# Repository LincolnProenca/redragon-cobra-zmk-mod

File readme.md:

# Custom ZMK Wireless Mouse: Redragon Cobra Mod 🖱️🐍

> **Hardware & Firmware Engineering Portfolio**

A comprehensive hardware and firmware project focused on creating a custom wireless mouse, built upon the Zephyr/ZMK ecosystem. A core idea behind this project was to create a versatile tool that seamlessly transitions between my work and home environments.

The project involved **designing a custom PCB**, specifically tailored to fit perfectly within the ergonomic shell of a **Redragon Cobra**. A key goal was to reuse as many components from the original mouse as possible—such as the switches and the wheel mechanism—transforming a traditional wired mouse into a premium, high-performance wireless tool.

Focused on energy efficiency, multiple productivity layers (Office/Gaming), and RGB Underglow lighting, the development overcame several electrical and logical challenges, especially in integrating high-consumption components (LEDs) with a _low-power_ sensor architecture.

## 📸 Project Gallery (Build Log)

<div align="center">

</div>
<br/>
<div align="center">

</div>

## 🛠️ Hardware Specifications & Custom PCB

The hardware architecture was custom-developed to reuse the Redragon Cobra shell and its main functional components (like the original clicks and side switches). The integration includes:

- **Microcontroller:** SuperMini nRF52 (nice!nano alternative based on the nRF52840)
- **Optical Sensor:** PixArt PMW3610 (Since the original was a wired sensor, it was replaced with this Low-Power architecture ideal for wireless)
- **Scroll / Wheel:** TTC Gold 13mm Rotary Encoder (The original encoder was damaged and an exact replacement wasn't available, so it was swapped for this equivalent TTC Gold)
- **Lighting:** WS2812 LED Strip (9 LEDs for underglow)
- **Battery:** 1200mAh 3.7V LiPo (Model 503048, 5x30x48mm)
- **LED Power Control:** Two-stage power-gating circuit (level shifter): an **A19T P-channel MOSFET**(salvaged from a damaged SuperMini) switches the raw battery line (B+) to the LED strip VCC, and its gate is driven by an **SS8050 NPN transistor** (label Y1, salvaged from the original Redragon Cobra PCB) acting as a level shifter. The NPN base is driven by the MCU's `EXT_POWER` pin (GPIO 1.11) through a ~1.4k base resistor (also salvaged from the damaged SuperMini). This guarantees full enhancement and full cut-off of the MOSFET across the entire battery range (3.0V–4.2V).

## ✨ Features and Functionalities

The firmware was designed to act as a hybrid device (Mouse + Keyboard), allowing the execution of complex macros and direct shortcuts on the board.

### Layer System

- **Gaming Layer (Default):** Standard mouse commands (LCLK, RCLK, MCLK, MB4, MB5) with high-sensitivity scroll.
- **Office Layer:** Transforms the mouse into a productivity tool focused on **Simulink** environments. Features built-in macros (`Ctrl + .`, `C`, `E`, `N`, `T`, `E`, `R`) injected in 30ms for quick alignments, compiling, and block organization.
- **Utility Layer (Bluetooth Modifier):** Holding the "Top 3" button transforms the main clicks into a Bluetooth remote control (Force Slot 0, Force Slot 1, Format Memory).

### Physical Combos

- **TOP_1 + TOP_2:** Clean Soft Off (cuts `EXT_POWER` first, then enters deep sleep).
- **TOP_1 + TOP_3:** Toggle RGB On/Off.
- **TOP_2 + TOP_3:** Next RGB effect.
- **SIDE_1 + SIDE_2:** System Reset (Hardware sys_reset).
- **Bottom Button:** Directly triggers System Reset.

> Combos were deliberately moved off the main click buttons (LMB/RMB/MMB): any key position participating in a combo is held for up to `timeout-ms` on every press, which added perceptible latency to middle-click drags.

## ⚡ Engineering Notes & Hardware Solutions

During development, several electrical integration and mechanical design bottlenecks were resolved. If you intend to replicate this project, pay attention to the following design decisions and topology rules:

### 1. PCB Modeling and Component Alignment

Without schematics for the original Redragon Cobra PCB, the new board had to be modeled from scratch. The PCB outline and component placements were reverse-engineered using top-down photos of the original board and a physical ruler for scale.

### 2. 3D Modeling for Fitment Check

To ensure the SuperMini, LiPo battery, and all reused components would fit within the limited internal space of the original shell, a full 3D model of the assembly was created. This step was crucial to guarantee clearance for the new components without modifying the external plastics.

### 3. Wired to Wireless Conversion Challenges

Because the original Redragon Cobra was a wired mouse, several structural challenges were addressed:

- **Sensor Swap:** The original power-hungry wired sensor had to be replaced by the low-power PixArt PMW3610.
- **Charging Port Routing:** To utilize the original cable exit hole at the front of the mouse for charging, a custom-made male-to-female USB-C cable was fabricated. It routes power from the front of the mouse internally back to the SuperMini microcontroller.

### 4. Power Separation (Brownout Prevention)

The 9-LED WS2812 strip consumes up to ~180mA, which exceeds the chronic regulation capacity of the board's LDO, causing a _brownout_ (VCC drop to ~2.6V) if powered by the 3.3V pin.

- **Solution:** The board's VCC NPN Level Shifter + P-MOSFET)
  By default, WS2812 LEDs continuously drain quiescent current even when turned off (displaying black color) via software. To properly maximize battery life during sleep states, a hardware switch was implemented.

**The design constraint:** the LED strip is powered directly from the raw battery rail (B+), which swings between ~3.0V and 4.2V, while the MCU GPIOs only swing between 0V and 3.3V. Driving the gate of a P-channel MOSFET directly from a 3.3V GPIO is therefore unreliable: with a full battery (4.1V–4.2V), a logic-high GPIO produces a VGS of only about **-0.8V**, which is dangerously close to the low threshold voltage (VGS_th) of the A19T. A proper high-side switch needs the gate to be pulled all the way up to the source voltage (B+) to guarantee cut-off, and all the way down to GND to guarantee full enhancement — something a 3.3V GPIO cannot do on its own.

- **Solution (Hardware — two-stage level shifter):** The gate drive is handled by an **SS8050 NPN transistor** (label Y1, salvaged from the original Redragon Cobra PCB) wired as an open-collector level shifter:
  - **A19T P-MOSFET:** Source -> B+, Drain -> LED VCC, with a **10k pull-up resistor between Gate and Source** (keeps the MOSFET fully off by default).
  - **SS8050 NPN:** Collector -> A19T Gate, Emitter -> GND, Base -> `EXT_POWER` GPIO **1.11** through a **~1.4k base resistor** (salvaged from a damaged SuperMini).
- **How it works:** when `EXT_POWER` is low, the NPN is cut off and the 10k resistor pulls the gate up to B+ (VGS = 0V), fully turning the MOSFET off regardless of battery voltage. When `EXT_POWER` goes high (3.3V), the NPN saturates and pulls the gate to GND, producing VGS = -B+ (up to -4.2V), fully enhancing the MOSFET with minimal RDS(on). Both states are now referenced to the correct rails, so the circuit switches cleanly across the whole battery range with no leakage and no heating.

### 6. Boot Noise (LEDs flashing electronic junk)

When powering up the board, the nRF52 has floating pins that injected noise into the WS2812 strip's data channel.

- **Solution (`.overlay`):** Insertion of the `bias-pull-down;` property on the `pinctrl` MOSI pin to anchor the signal at 0V during boot, coupled with the initialization delay `init-delay-ms = <350>;` to wait for the strip's capacitors.

### 7. Physical Surface Conditioning

**Known Limitation:** The PixArt PMW3610 has extremely weak optical emission to save battery. It **does not work properly on wool or felt mousepads**, as the three-dimensional fibers blur the lens. It requires the use of traditional microfiber (cloth/fabric) mousepads or rigid surfaces.

### 8. PCB Rev1 Limitations & Rev2 Updates

**Known Limitation (Rev1):** Revision 1 (rev1) of the custom PCB does not natively route the Battery (B+) directly to the LED's VCC, nor does it include footprints for the power-gating circuit. These modifications (A19T P-MOSFET, SS8050 NPN, and resistors) had to be manually bodged (hardwired) onto the physical board.

**Rev2 Architecture Overhaul:** To eliminate the bulky discrete transistor assembly, the **Revision 2 (rev2)** of the PCB replaces the entire BJT+MOSFET circuit with a single **TPS22917DBV Load Switch** (SOT-23-6). 

- **How it works:** The raw battery line (B+) connects directly to `VIN`, and the MCU's `EXT_POWER` pin (GPIO 1.11) drives the `ON` pin directly. Since the TPS22917 features an internal smart level-shifter, it seamlessly interfaces a 3.3V GPIO with the fluctuating 3.0V–4.2V battery rail, ensuring a clean cut-off with sub-microampere leakage current.
- **Quick Discharge:** The `QOD` pin is tied directly to `VOUT` to leverage the internal 150Ω discharge resistor, instantly draining the LED strip's capacitors during sleep transitions.

> [!WARNING]
> **Rev2 Disclaimer:** While the Rev2 layout integrates these native traces, capacitors (1μ F input / 0.1μ F output), and the SOT-23-6 footprint, **this board revision has not been physically manufactured or tested yet**. If you plan to order it, please review the schematics and Gerber files carefully.

---

_Status: v1.0 (Full logical functionality validated in Hardware)._

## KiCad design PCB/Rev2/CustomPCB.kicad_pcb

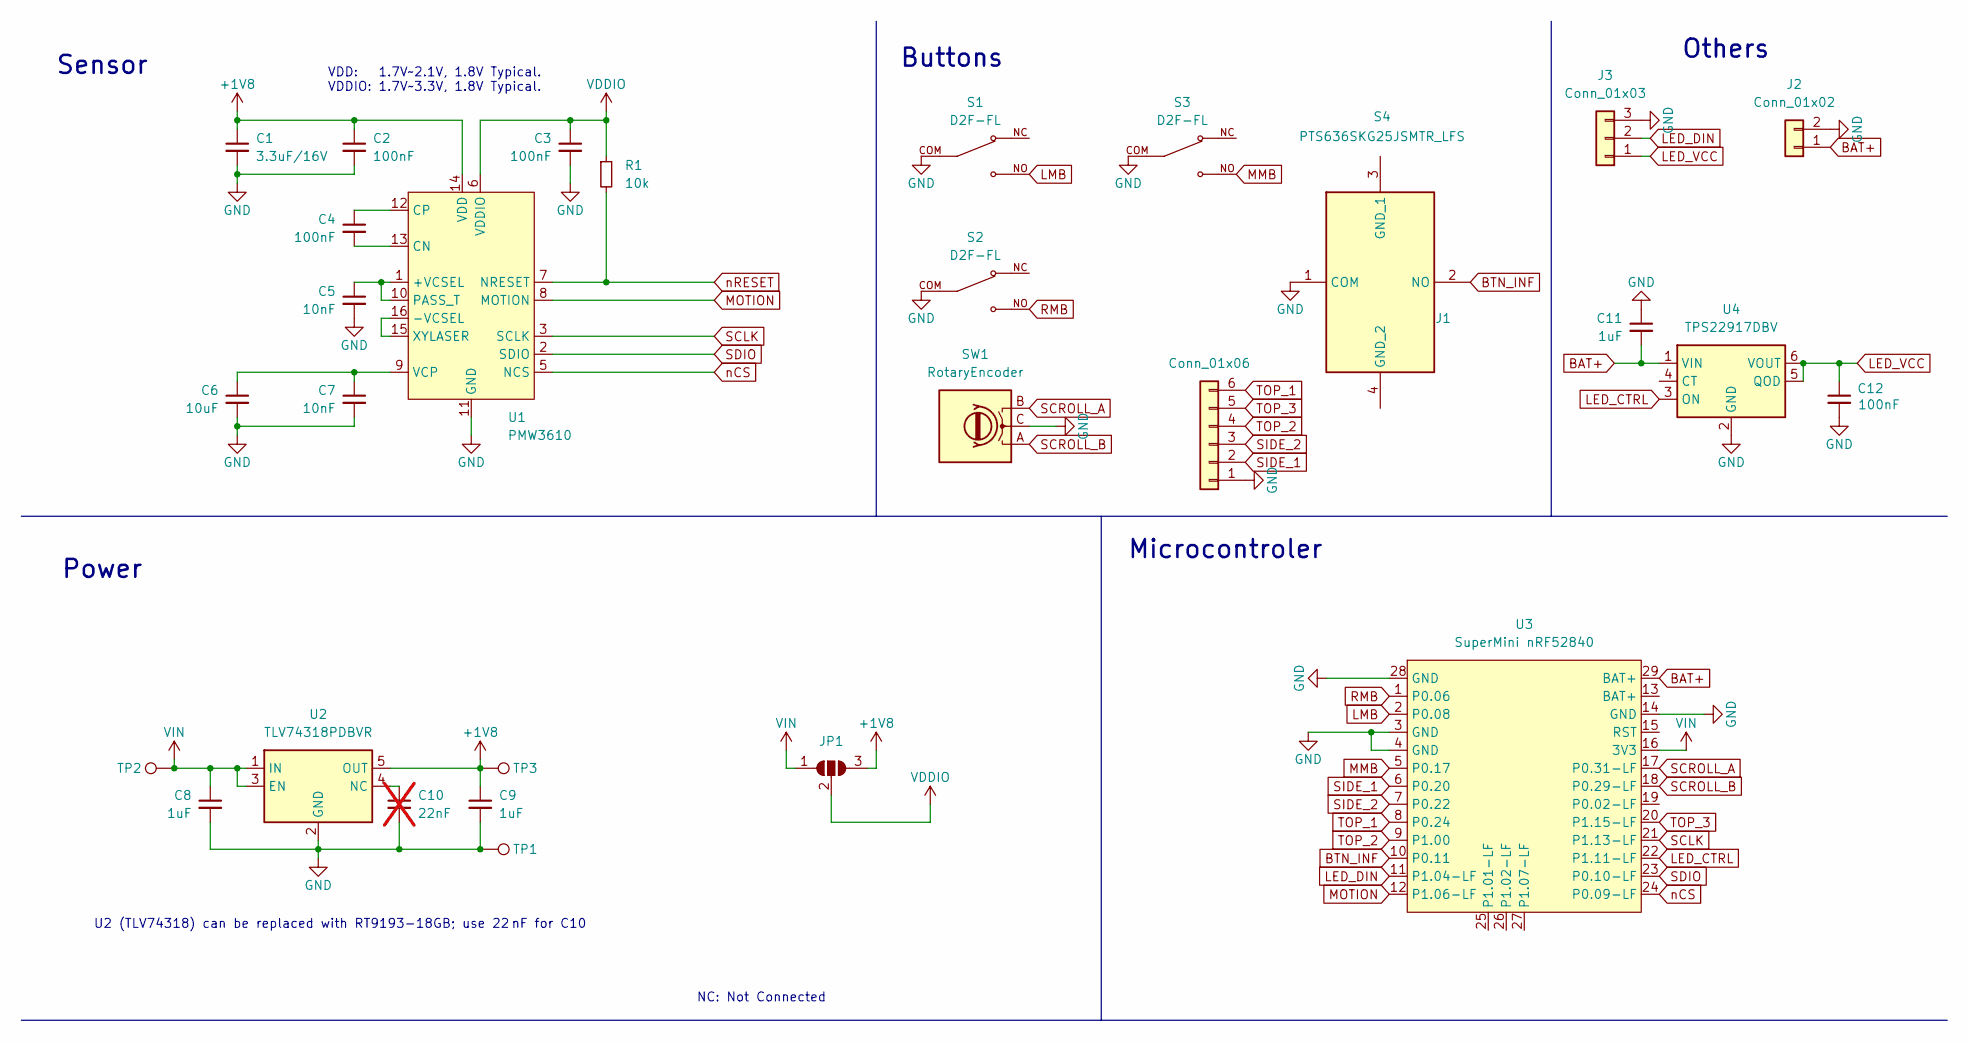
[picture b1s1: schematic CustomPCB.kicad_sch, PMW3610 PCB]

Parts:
C1: 3.3uF/16V; C_0805_2012Metric; MFR. Part # TCC0805X7R335K250FT; JLCPCB Part # C7393948
C2, C3, C4, C12: 100nF; C_0603_1608Metric; MFR. Part # CC0603KRX7R9BB104; JLCPCB Part # C14663
C5, C7: 10nF; C_0603_1608Metric; MFR. Part # 0603B103K500NT; JLCPCB Part # C57112
C6: 10uF; C_0805_2012Metric; MFR. Part # CL21A106KAYNNNE; JLCPCB Part # C15850
C8, C9: 1uF; C_0603_1608Metric; MFR. Part # CL10A105KB8NNNC; JLCPCB Part # C15849
C10: 22nF; C_0603_1608Metric; MFR. Part # CL10B223KB8NNNC; JLCPCB Part # C21122; not fitted
C11: 1uF; C_0603_1608Metric
J1: Conn_01x06; Molex_PicoBlade_53047-0610_1x06_P1.25mm_Vertical
J2: Conn_01x02; PinHeader_1x02_P2.54mm_Vertical
J3: Conn_01x03; PinHeader_1x03_P2.54mm_Vertical
JP1: SolderJumper_3_Open; SolderJumper-3_P1.3mm_Open_RoundedPad1.0x1.5mm_NumberLabels
R1: 10k; R_0603_1608Metric; MFR. Part # 0603WAF1002T5E; JLCPCB Part # C25804
S1, S2, S3: D2F-FL; SW_D2F-FL; PARTREV N/A
S4: PTS636SKG25JSMTR_LFS; PTS636SKG25JSMTRLFS; Mouser Part Number 611-PTS636SKG25JSMTR
SW1: RotaryEncoder; Rotary_Encoder
TP1, TP2, TP3: TestPoint; TestPoint_Pad_D1.5mm
U1: PMW3610; PMW3610DM-SUDU 16Pin; MFR. Part # PMW3610DM-SUDU; JLCPCB Part # C42442560
U2: TLV74318PDBVR; SOT-23-5_HandSoldering; MFR. Part # TLV74318PDBVR; JLCPCB Part # C485152
U3: SuperMini nRF52840; SuperMini NRF52840
U4: TPS22917DBV; SOT-23-6

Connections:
+1V8: C1.1, C2.1, C9.1, JP1.3 (B), TP3.1 (1_1), U1.14 (VDD), U2.5 (OUT)
BAT+: C11.2, J2.1, U3.29 (BAT+), U4.1 (VIN)
BTN_INF: S4.2 (NO), U3.10 (P0.11)
GND: C1.2, C2.2, C3.2, C5.2, C6.2, C7.2, C8.2, C9.2, C10.2, C11.1, C12.2, J1.1, J2.2, J3.3, S1.COM, S2.COM, S3.COM, S4.1 (COM), SW1.C, TP1.1 (1_1), U1.11 (GND), U2.2 (GND), U3.3 (GND), U3.4 (GND), U3.14 (GND), U3.28 (GND), U4.2 (GND)
LED_CTRL: U3.22 (P1.11-LF), U4.3 (ON)
LED_DIN: J3.2, U3.11 (P1.04-LF)
LED_VCC: C12.1, J3.1, U4.5 (QOD), U4.6 (VOUT)
LMB: S1.NO, U3.2 (P0.08)
MMB: S3.NO, U3.5 (P0.17)
MOTION: U1.8 (MOTION), U3.12 (P1.06-LF)
unnamed: C5.1, U1.1 (+VCSEL), U1.10 (PASS_T)
unnamed: U1.15 (XYLASER), U1.16 (-VCSEL)
unnamed: C4.2, U1.13 (CN)
unnamed: C4.1, U1.12 (CP)
unnamed: C6.1, C7.1, U1.9 (VCP)
unnamed: C10.1, U2.4 (NC)
RMB: S2.NO, U3.1 (P0.06)
SCLK: U1.3 (SCLK), U3.21 (P1.13-LF)
SCROLL_A: SW1.B, U3.17 (P0.31-LF)
SCROLL_B: SW1.A, U3.18 (P0.29-LF)
SDIO: U1.2 (SDIO), U3.23 (P0.10-LF)
SIDE_1: J1.2, U3.6 (P0.20)
SIDE_2: J1.3, U3.7 (P0.22)
TOP_1: J1.6, U3.8 (P0.24)
TOP_2: J1.4, U3.9 (P1.00)
TOP_3: J1.5, U3.20 (P1.15-LF)
VDDIO: C3.1, JP1.2 (C), R1.1, U1.6 (VDDIO)
VIN: C8.1, JP1.1 (A), TP2.1 (1_1), U2.1 (IN), U2.3 (EN), U3.16 (3V3)
nCS: U1.5 (NCS), U3.24 (P0.09-LF)
nRESET: R1.2, U1.7 (NRESET)

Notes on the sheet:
Others
Microcontroler
U2 (TLV74318) can be replaced with RT9193-18GB; use 22 nF for C10
Sensor
Power
NC: Not Connected
Buttons
VDD: 1.7V~2.1V, 1.8V Typical. VDDIO: 1.7V~3.3V, 1.8V Typical.

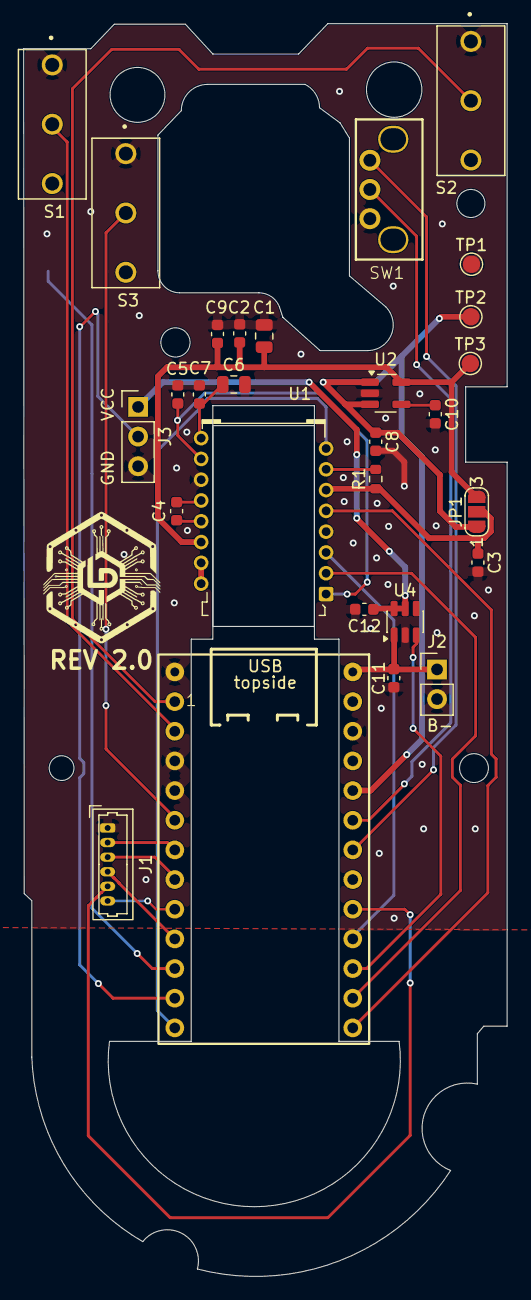
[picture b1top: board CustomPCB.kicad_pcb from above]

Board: 2 copper layers, 41.4 x 107.3 mm, 30 parts (1 on the bottom side), 30 nets.

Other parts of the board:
REV 2.0: LOGO; logo

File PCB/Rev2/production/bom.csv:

Designator,Footprint,Quantity,Value,LCSC Part #
C1,0805,1,3.3uF/16V,C7393948
C10,0603,1,22nF,C21122
C11,0603,1,1uF,
"C12, C2, C3, C4",0603,4,100nF,C14663
"C5, C7",0603,2,10nF,C57112
C6,0805,1,10uF,C15850
"C8, C9",0603,2,1uF,C15849
J1,Molex_PicoBlade_53047-0610_1x06_P1.25mm_Vertical,1,Conn_01x06,
J2,PinHeader_1x02_P2.54mm_Vertical,1,Conn_01x02,
J3,PinHeader_1x03_P2.54mm_Vertical,1,Conn_01x03,
R1,0603,1,10k,C25804
"S1, S2, S3",SW_D2F-FL,3,D2F-FL,
S4,PTS636SKG25JSMTRLFS,1,PTS636SKG25JSMTR_LFS,
SW1,Rotary_Encoder,1,RotaryEncoder,
U1,PMW3610DM-SUDU 16Pin,1,PMW3610,C42442560
U2,SOT-23-5_HandSoldering,1,TLV74318PDBVR,C485152
U4,SOT-23-6,1,TPS22917DBV,

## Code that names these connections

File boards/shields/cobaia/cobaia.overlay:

#include <zephyr/dt-bindings/input/input-event-codes.h>
#include <zephyr/dt-bindings/led/led.h>
#include <dt-bindings/zmk/matrix_transform.h>
#include <input/processors.dtsi>

/ {
    chosen {
        zmk,kscan = &kscan0;
        zmk,underglow = &led_strip;
        zmk,pointing = &pmw3610;
    };

    /*
     * LED power gating: two-stage level shifter.
     * - A19T P-MOSFET switches B+ to the LED strip VCC (source=B+, drain=LED VCC,
     *   10k pull-up between gate and source keeps it off by default).
     * - The gate is driven by an SS8050 NPN (open-collector level shifter):
     *   collector=gate, emitter=GND, base=GPIO 1.11 via ~1.4k.
     * - GPIO high (3.3V) saturates the NPN, pulling the gate to GND (VGS=-B+,
     *   full enhancement). GPIO low releases the gate to B+ via the 10k pull-up
     *   (VGS=0, full cut-off at any battery voltage).
     */
    EXT_POWER: EXT_POWER {
        compatible = "zmk,ext-power-generic";
        control-gpios = <&gpio0 13 GPIO_ACTIVE_HIGH>, <&gpio1 11 GPIO_ACTIVE_HIGH>;
        init-delay-ms = <350>;
    };

    kscan0: kscan_0 {
        compatible = "zmk,kscan-gpio-direct";
        wakeup-source;
        input-gpios
            = <&gpio0  8 (GPIO_ACTIVE_LOW | GPIO_PULL_UP)>   /* LMB */
            , <&gpio0  6 (GPIO_ACTIVE_LOW | GPIO_PULL_UP)>   /* RMB */
            , <&gpio0 17 (GPIO_ACTIVE_LOW | GPIO_PULL_UP)>   /* MMB */
            , <&gpio0 20 (GPIO_ACTIVE_LOW | GPIO_PULL_UP)>   /* SIDE_1 */
            , <&gpio0 22 (GPIO_ACTIVE_LOW | GPIO_PULL_UP)>   /* SIDE_2 */
            , <&gpio0 24 (GPIO_ACTIVE_LOW | GPIO_PULL_UP)>   /* TOP_1 */
            , <&gpio1  0 (GPIO_ACTIVE_LOW | GPIO_PULL_UP)>   /* TOP_2 */
            , <&gpio1 15 (GPIO_ACTIVE_LOW | GPIO_PULL_UP)>   /* TOP_3 */
            , <&gpio0 11 (GPIO_ACTIVE_LOW | GPIO_PULL_UP)>   /* BTN_INF */
            ;
    };

    left_encoder: encoder_left {
        compatible = "alps,ec11";
        a-gpios = <&gpio0 31 (GPIO_ACTIVE_LOW | GPIO_PULL_UP)>; /* SCROLL_A */
        b-gpios = <&gpio0 29 (GPIO_ACTIVE_LOW | GPIO_PULL_UP)>; /* SCROLL_B */
        steps = <24>;
        status = "okay";
    };

    sensors {
        compatible = "zmk,keymap-sensors";
        sensors = <&left_encoder>;
        triggers-per-rotation = <24>;
    };

    pmw3610_listener {
        compatible = "zmk,input-listener";
        device = <&pmw3610>;

        /* If Layer 1 is active, multiply the speed by 4/5 (1000 -> 800 DPI) */
        layer_slow {
            layers = <1>;
            input-processors = <&zip_xy_scaler 4 5>;
        };

        /* If Layer 2 is active, multiply the speed by 6/5 (1000 -> 1200 DPI) */
        layer_fast {
            layers = <2>;
            input-processors = <&zip_xy_scaler 6 5>;
        };
    };
};

&pinctrl {
    spi1_default: spi1_default {
        group1 {
            psels = <NRF_PSEL(SPIM_SCK, 1, 13)>,         /* SCLK */
                    <NRF_PSEL(SPIM_MOSI, 0, 10)>,        /* SDIO (TX) */
                    <NRF_PSEL(SPIM_MISO, 0, 10)>;        /* SDIO (RX) */
        };
    };

    spi1_sleep: spi1_sleep {
        group1 {
            psels = <NRF_PSEL(SPIM_SCK, 1, 13)>,
                    <NRF_PSEL(SPIM_MOSI, 0, 10)>,
                    <NRF_PSEL(SPIM_MISO, 0, 10)>;
            low-power-enable;
        };
    };
    
    spi3_default: spi3_default {
        group1 {
            psels = <NRF_PSEL(SPIM_MOSI, 1, 4)>;         /* LED_DIN */
            bias-pull-down;
        };
    };

    spi3_sleep: spi3_sleep {
        group1 {
            psels = <NRF_PSEL(SPIM_MOSI, 1, 4)>;
            low-power-enable;
        };
    };
};

&spi1 {
    status = "okay";
    compatible = "nordic,nrf-spim";
    pinctrl-0 = <&spi1_default>;
    pinctrl-1 = <&spi1_sleep>;
    pinctrl-names = "default", "sleep";
    cs-gpios = <&gpio0 9 GPIO_ACTIVE_LOW>;               

    pmw3610: pmw3610@0 {
        status = "okay";
        compatible = "pixart,pmw3610-alt";
        reg = <0>;
        spi-max-frequency = <2000000>;
        irq-gpios = <&gpio1 6 (GPIO_ACTIVE_LOW | GPIO_PULL_UP)>; 
        
        /* INPUT SUBSYSTEM UPDATE */
        evt-type = <INPUT_EV_REL>;
        x-input-code = <INPUT_REL_X>;
        y-input-code = <INPUT_REL_Y>;
        
        /* BASE HARDWARE CPI DEFINITION */
        cpi = <1000>;
        
        /* invert-y; */
        invert-x;
        swap-xy;
    };
};

&spi3 {
    status = "okay";
    compatible = "nordic,nrf-spim";
    pinctrl-0 = <&spi3_default>;
    pinctrl-1 = <&spi3_sleep>;
    pinctrl-names = "default", "sleep";
    
    led_strip: ws2812@0 {
        compatible = "worldsemi,ws2812-spi";
        reg = <0>;
        spi-max-frequency = <4000000>;
        chain-length = <9>;
        spi-one-frame = <0x70>;
        spi-zero-frame = <0x40>;
        color-mapping = <2 1 3>;
    };
};

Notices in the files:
PCB/CustomPCB/CustomPCB.kicad_sch:
Open Source Hardware, CERN-OHL-P v2
